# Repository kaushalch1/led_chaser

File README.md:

# Compass LED Chaser 

The **Compass LED Chaser** is a travel based PCB project that combines the pcb with the cad model.it is Designed in the shape of a compass, the board features eight LEDs arranged around the compass points. The LEDs illuminate sequentially, it can be used for  adventure, and the excitement of discovering new destinations.

Powered via **USB Type-C**, the project is portable and can be used with a power bank, laptop, or USB charger, making it an ideal travel companion or desk decoration.

Rather than simply blinking LEDs, the board represents movement, direction, and the journey toward the next adventure.
And also we can store the pcb in the special case

## Features

- Compass-shaped PCB
- Eight LEDs arranged around the compass
- Sequential LED chasing effect
- Adjustable animation speed
- USB Type-C powered
- ON/OFF power switch
- Reset button to restart the sequence
- Compact and portable design
- Beginner-friendly digital electronics project

---
## Why I Made This Project

Most beginner LED projects are just a few LEDs blinking on a rectangular board. i wanted to make something that had a theme, and travel is something I love.

a compass stands for exploration and choosing where to go next. So I designed a PCB in the shape of a compass, with eight LEDs placed at the compass points with 8 directions.

The result is a small, portable board that works as a decorative travel accessory.
## Components Used
**Total Estimated Cost: $3.30 USD**

| Name | Purpose | Quantity | Total Cost (USD) | Link | Distributor |
|---|---|---:|---:|---|---|
| CD4017BE (DIP-16) | Decade counter (LED sequencer) | 1 | 0.76 | [Link](https://www.lcsc.com/product-detail/C34519.html) | LCSC |
| Bourns 3296W-1-503LF 50k trimmer | Speed adjust potentiometer | 1 | 0.92 | [Link](https://www.lcsc.com/product-detail/C83686.html) | LCSC |
| NE555P (DIP-8) | Clock oscillator timer | 1 | 0.33 | [Link](https://www.lcsc.com/product-detail/C46749.html) | LCSC |
| USB-C receptacle (TYPE-C-31-M-12) | USB-C power input | 1 | 0.19 | [Link](https://www.lcsc.com/product-detail/C165948.html) | LCSC |
| Tactile switch SMD (Omron B3S-1000) | Switch SW1 | 1 | 0.25 | [Link](https://www.lcsc.com/search?q=B3S-1000) | LCSC |
| LED 3mm THT | Chaser LEDs | 8 | 0.24 | [Link](https://www.lcsc.com/search?q=3mm+LED+THT) | LCSC |
| Resistors 1/4W axial (1k, 5.1k, 330R, 10k) | LED, timing, pull-down and CC resistors | 12 | 0.12 | [Link](https://www.lcsc.com/search?q=1%2F4W+axial+resistor) | LCSC |
| Tact switch 6mm THT | Switch SW2 | 1 | 0.04 | [Link](https://www.lcsc.com/search?q=tactile+switch+6x6+THT) | LCSC |
| 1uF radial electrolytic capacitor (5mm) | Timing/filter capacitor | 1 | 0.03 | [Link](https://www.lcsc.com/search?q=1uF+radial+electrolytic) | LCSC |
| 10nF disc ceramic capacitor (5mm) | Control-pin decoupling capacitor | 1 | 0.02 | [Link](https://www.lcsc.com/search?q=10nF+disc+ceramic+capacitor) | LCSC |
| PCB (bare board) | Main PCB | 1 | 0.40 | [Link](https://jlcpcb.com/) | JLCPCB |

## Travel Applications

Although designed primarily as an educational electronics project, the Compass LED Chaser has several travel-themed uses:
- Decorative travel desk accessory
- Portable campsite or hostel mood light
- Gift for travel and adventure enthusiasts

The Compass LED Chaser represents the excitement of exploration and the joy of travel. Each rotating LED symbolizes taking the next step toward discovering new places, cultures, and experiences. It serves as a reminder that every adventure starts by choosing a direction and moving forward.
## How To Use It
Plug a usb Type-C cable into the board.
Slide the switch to ON. The LEDs start chasing around the compass.
Press the reset button to restart the sequence from the first LED.
Slide the switch to OFF and close the lid when travelling.
schematic files

pcb files

full assembly

## 3d
case top view:

case bottom view:

middle panel on pcb:

top lid:

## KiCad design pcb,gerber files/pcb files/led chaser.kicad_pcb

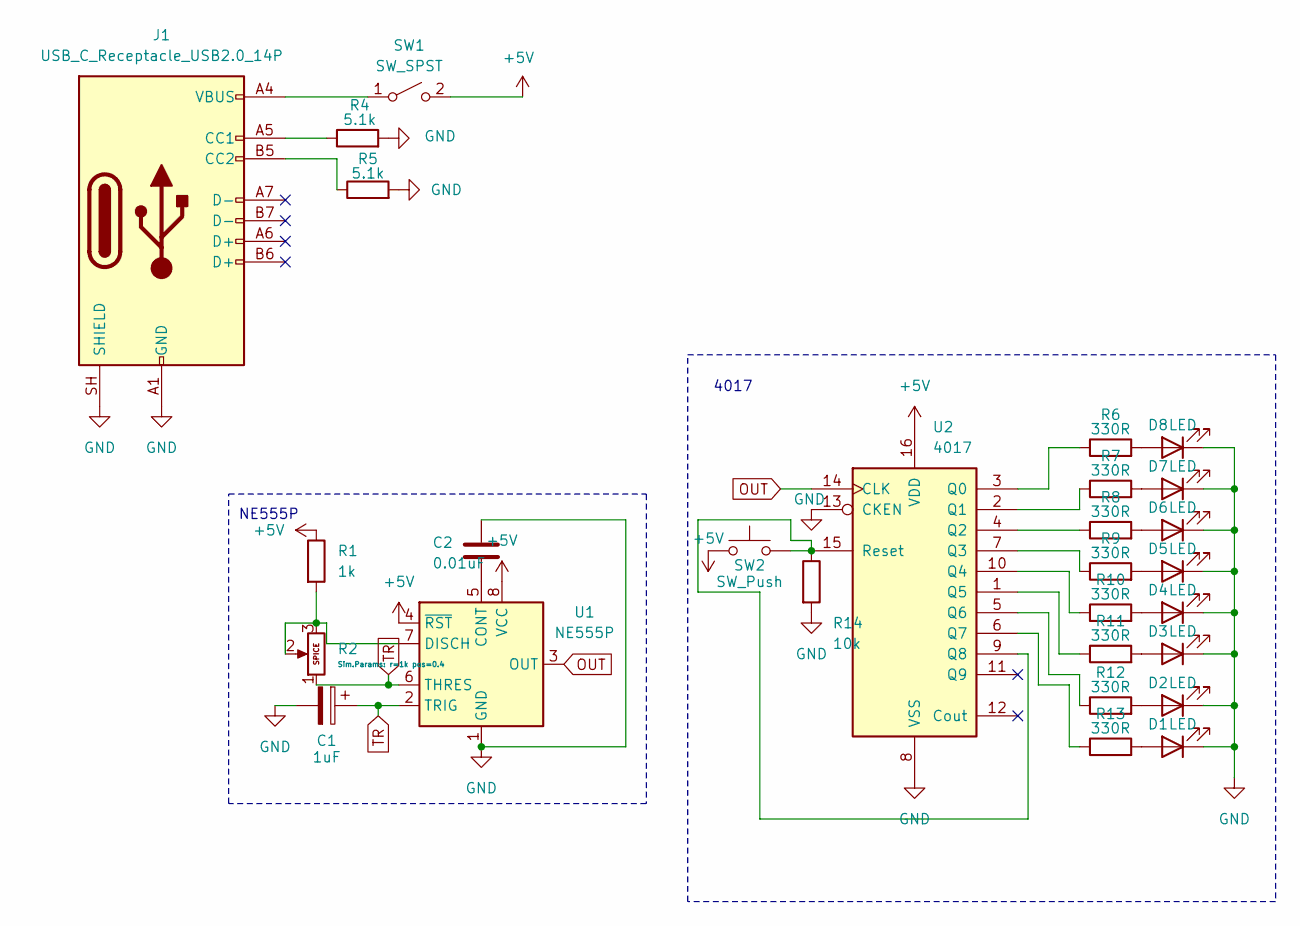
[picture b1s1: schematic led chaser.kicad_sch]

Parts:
C1: 1uF; CP_Radial_D5.0mm_P2.00mm
C2: 0.01uF; C_Disc_D4.7mm_W2.5mm_P5.00mm
D1, D2, D3, D4, D5, D6, D7, D8: LED; LED_D3.0mm
J1: USB_C_Receptacle_USB2.0_14P; USB_C_Receptacle_HRO_TYPE-C-31-M-12
R1: 1k; R_Axial_DIN0207_L6.3mm_D2.5mm_P7.62mm_Horizontal
R2: 50k; Potentiometer_Bourns_3296W_Vertical
R4, R5: 5.1k; R_Axial_DIN0207_L6.3mm_D2.5mm_P7.62mm_Horizontal
R6, R7, R8, R9, R10, R11, R12, R13: 330R; R_Axial_DIN0207_L6.3mm_D2.5mm_P7.62mm_Horizontal
R14: 10k; R_Axial_DIN0207_L6.3mm_D2.5mm_P7.62mm_Horizontal
SW1: SW_SPST; SW_SPST_B3S-1000
SW2: SW_Push; SW_PUSH_6mm
U1: NE555P; DIP-8_W7.62mm
U2: 4017; DIP-16_W7.62mm

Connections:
+5V: R1.1, SW1.2 (B), SW2.1, U1.4 (~RST), U1.8 (VCC), U2.16 (VDD)
GND: C1.2, C2.1, D1.1 (K), D2.1 (K), D3.1 (K), D4.1 (K), D5.1 (K), D6.1 (K), D7.1 (K), D8.1 (K), J1.A1 (GND), J1.A12 (GND), J1.B1 (GND), J1.B12 (GND), J1.SH (SHIELD), R4.2, R5.2, R14.2, U1.1 (GND), U2.8 (VSS), U2.13 (CKEN)
unnamed: D1.2 (A), R13.2
unnamed: D2.2 (A), R12.2
unnamed: D3.2 (A), R11.2
unnamed: D4.2 (A), R10.2
unnamed: D5.2 (A), R9.2
unnamed: D6.2 (A), R8.2
unnamed: D7.2 (A), R7.2
unnamed: D8.2 (A), R6.2
unnamed: J1.A5 (CC1), R4.1
unnamed: J1.B5 (CC2), R5.1
unnamed: J1.A4 (VBUS), J1.A9 (VBUS), J1.B4 (VBUS), J1.B9 (VBUS), SW1.1 (A)
unnamed: C2.2, U1.5 (CONT)
unnamed: R1.2, R2.2, R2.3, U1.7 (DISCH)
unnamed: R6.1, U2.3 (Q0)
unnamed: R7.1, U2.2 (Q1)
unnamed: R8.1, U2.4 (Q2)
unnamed: R9.1, U2.7 (Q3)
unnamed: R10.1, U2.10 (Q4)
unnamed: R11.1, U2.1 (Q5)
unnamed: R12.1, U2.5 (Q6)
unnamed: R13.1, U2.6 (Q7)
unnamed: R14.1, SW2.2, U2.9 (Q8), U2.15 (Reset)
OUT: U1.3 (OUT), U2.14 (CLK)
TR: C1.1, R2.1, U1.2 (TRIG), U1.6 (THRES)

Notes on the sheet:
NE555P
4017

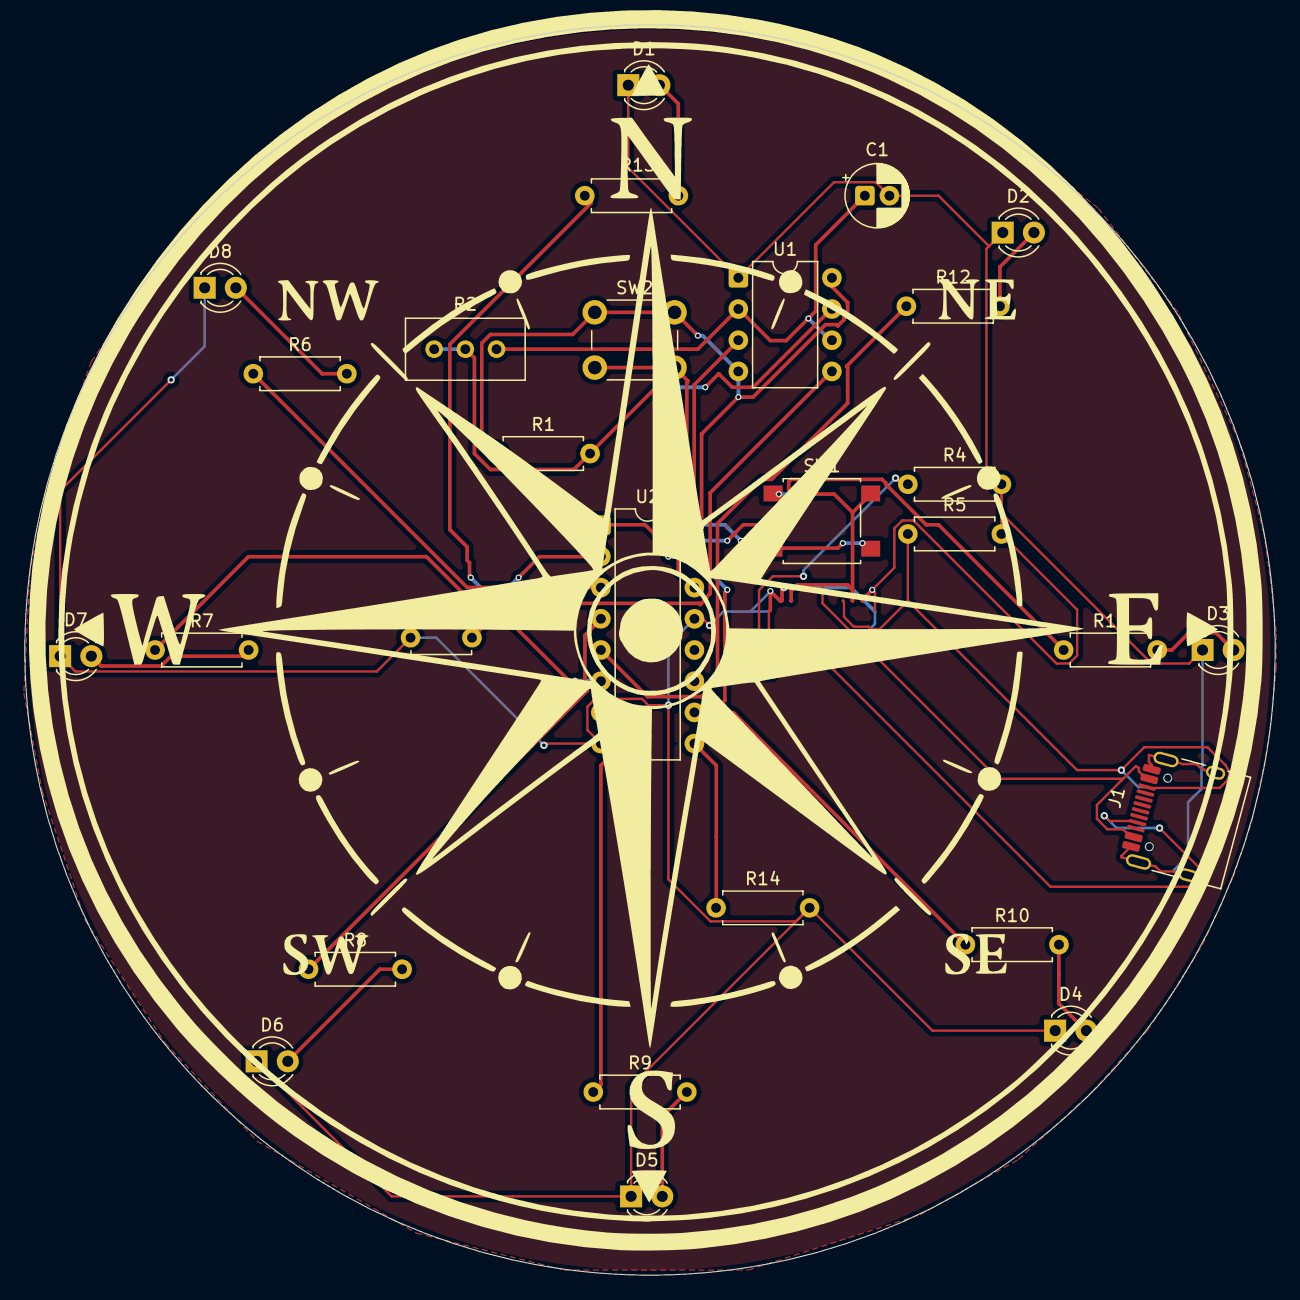
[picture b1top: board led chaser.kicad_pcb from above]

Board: 2 copper layers, 101.8 x 101.8 mm, 28 parts (0 on the bottom side), 26 nets.
